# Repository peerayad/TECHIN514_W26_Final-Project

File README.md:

# TECHIN514_W26_Final-Project
## Project Title: Motion-Activated Wake-Up Alarm System

 An alarm clock system with an ankle-worn strap that uses an accelerometer to detect walking movement. The alarm continues ringing until the user gets out of bed and walks for three consecutive minutes, ensuring they are fully awake before the alarm stops.

---------

## 1.Sensor Device: Ankle Strap Motion Sensor

The ankle strap is a wearable sensor device built on a custom-designed PCB. It is designed to be lightweight and compact while reliably detecting walking motion and communicating wirelessly with the bedside alarm unit.

### Hardware Components

- Microcontroller: Seeed Studio XIAO ESP32-C3 (Bluetooth Low Energy)
- Accelerometer: LIS3DH 3-axis accelerometer
- Battery: 3.7V 100mAh LiPo battery (with protection circuit)

### How It Works

The LIS3DH accelerometer measures 3-axis motion data to detect walking activity. The ESP32-C3 processes this data and determines whether continuous walking is occurring. When walking is detected, the device tracks elapsed walking time and transmits status updates to the display unit using Bluetooth Low Energy (BLE). Power consumption is minimized through motion-based interrupts and deep sleep modes.

### Power Design
The custom PCB integrates a 3.7V 100mAh LiPo battery with onboard charging and regulation. This battery capacity provides sufficient peak current for BLE transmission while keeping the device small and wearable.

------

## 2.Display Device: Bedside Alarm Unit

The display device is a bedside alarm unit responsible for alerting the user and confirming when the walking requirement has been completed. It receives walking status data from the ankle strap sensor and controls the alarm behavior.

### Hardware Components

- Microcontroller: Seeed Studio XIAO ESP32-C3
- Alarm output: Piezo buzzer
- Visual indicator: LED indicator
- User input: Tactile push button
- Battery: 3.7V 100mAh LiPo battery (with protection circuit)

### How It Works

At the scheduled alarm time, the display device activates the buzzer and visual indicator. It receives walking status and elapsed walking time from the ankle strap via Bluetooth Low Energy (BLE). While the user is walking, the display provides visual feedback to indicate progress. Once three continuous minutes of walking are confirmed, the display device automatically stops the alarm.

### User Interaction

A single push button is used for basic interaction, such as set the alarm.The alarm cannot be permanently dismissed until the walking condition is satisfied.

----

## 3.1 Diagram

## 3.2 Workflow

### 3.3 Schematic

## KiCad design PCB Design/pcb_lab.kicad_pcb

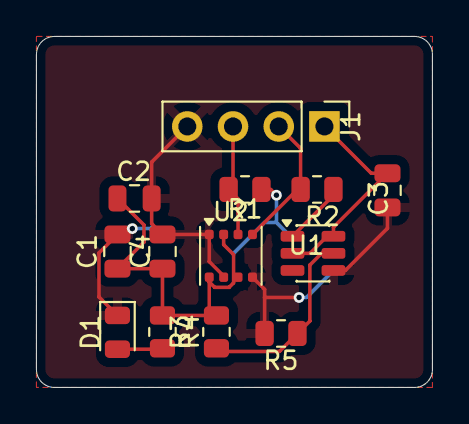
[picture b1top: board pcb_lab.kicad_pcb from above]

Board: 2 copper layers, 22.0 x 19.5 mm, 13 parts (0 on the bottom side), 7 nets.

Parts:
C1, C2, C3, C4: C; C_0805_2012Metric
D1: LED; LED_0805_2012Metric
J1: Conn_01x04; PinHeader_1x04_P2.54mm_Vertical
R1, R2, R3, R4, R5: R; R_0805_2012Metric
U1: ADP3331ARTZ-REEL7; SOT-23-6
U2: BME280; Bosch_LGA-8_3x3mm_P0.8mm_ClockwisePinNumbering

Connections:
+3V3: C1.1, C2.1, C4.1, R1.1, R2.1, R3.1, R4.1, U1.1 (OUT), U2.2 (CSB), U2.6 (VDDIO), U2.8 (VDD)
/SCL: J1.2, R2.2, U2.4 (SCK)
/SDA: J1.3, R1.2, U2.3 (SDI)
GND: C1.2, C2.2, C3.2, C4.2, D1.1 (K), J1.4, R5.2, U1.4 (GND), U2.1 (GND), U2.5 (SDO), U2.7 (GND)
unnamed: D1.2 (A), R3.2
unnamed: R4.2, R5.1, U1.5 (FB)
VCC: C3.1, J1.1, U1.2 (IN), U1.6 (~SD)

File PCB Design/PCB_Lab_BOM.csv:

"#","Reference","Qty","Value","Footprint","DNP"
"1","C1, C2, C3, C4","4","C","Capacitor_SMD:C_0805_2012Metric",""
"2","D1","1","LED","LED_SMD:LED_0805_2012Metric",""
"3","J1","1","Conn_01x04","Connector_PinHeader_2.54mm:PinHeader_1x04_P2.54mm_Vertical",""
"4","R1, R2, R3, R4, R5","5","R","Resistor_SMD:R_0805_2012Metric",""
"5","U1","1","ADP3331ARTZ-REEL7","Package_TO_SOT_SMD:SOT-23-6",""
"6","U2","1","BME280","Package_LGA:Bosch_LGA-8_3x3mm_P0.8mm_ClockwisePinNumbering",""

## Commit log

2026-01-20 Add description
2026-01-20 Add Description: Sensor and Display
2026-01-20 add datasheet
2026-01-20 Add diagram picture
2026-01-20 Add workflow
2026-01-20 Fix diagram and flow charge by adding LED
2026-01-20 fix picture
2026-01-20 add devices picture
2026-01-20 add speaker datasheet
2026-01-26 add schematic
2026-01-26 add schematic picture on readme
2026-01-26 change file name to BOM
2026-01-30 add PCB lab
2026-02-08 add spread sheet power model
2026-02-08 Update datasheet
